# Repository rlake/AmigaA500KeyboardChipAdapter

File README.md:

Amiga A500 Keyboard Chip Adapter

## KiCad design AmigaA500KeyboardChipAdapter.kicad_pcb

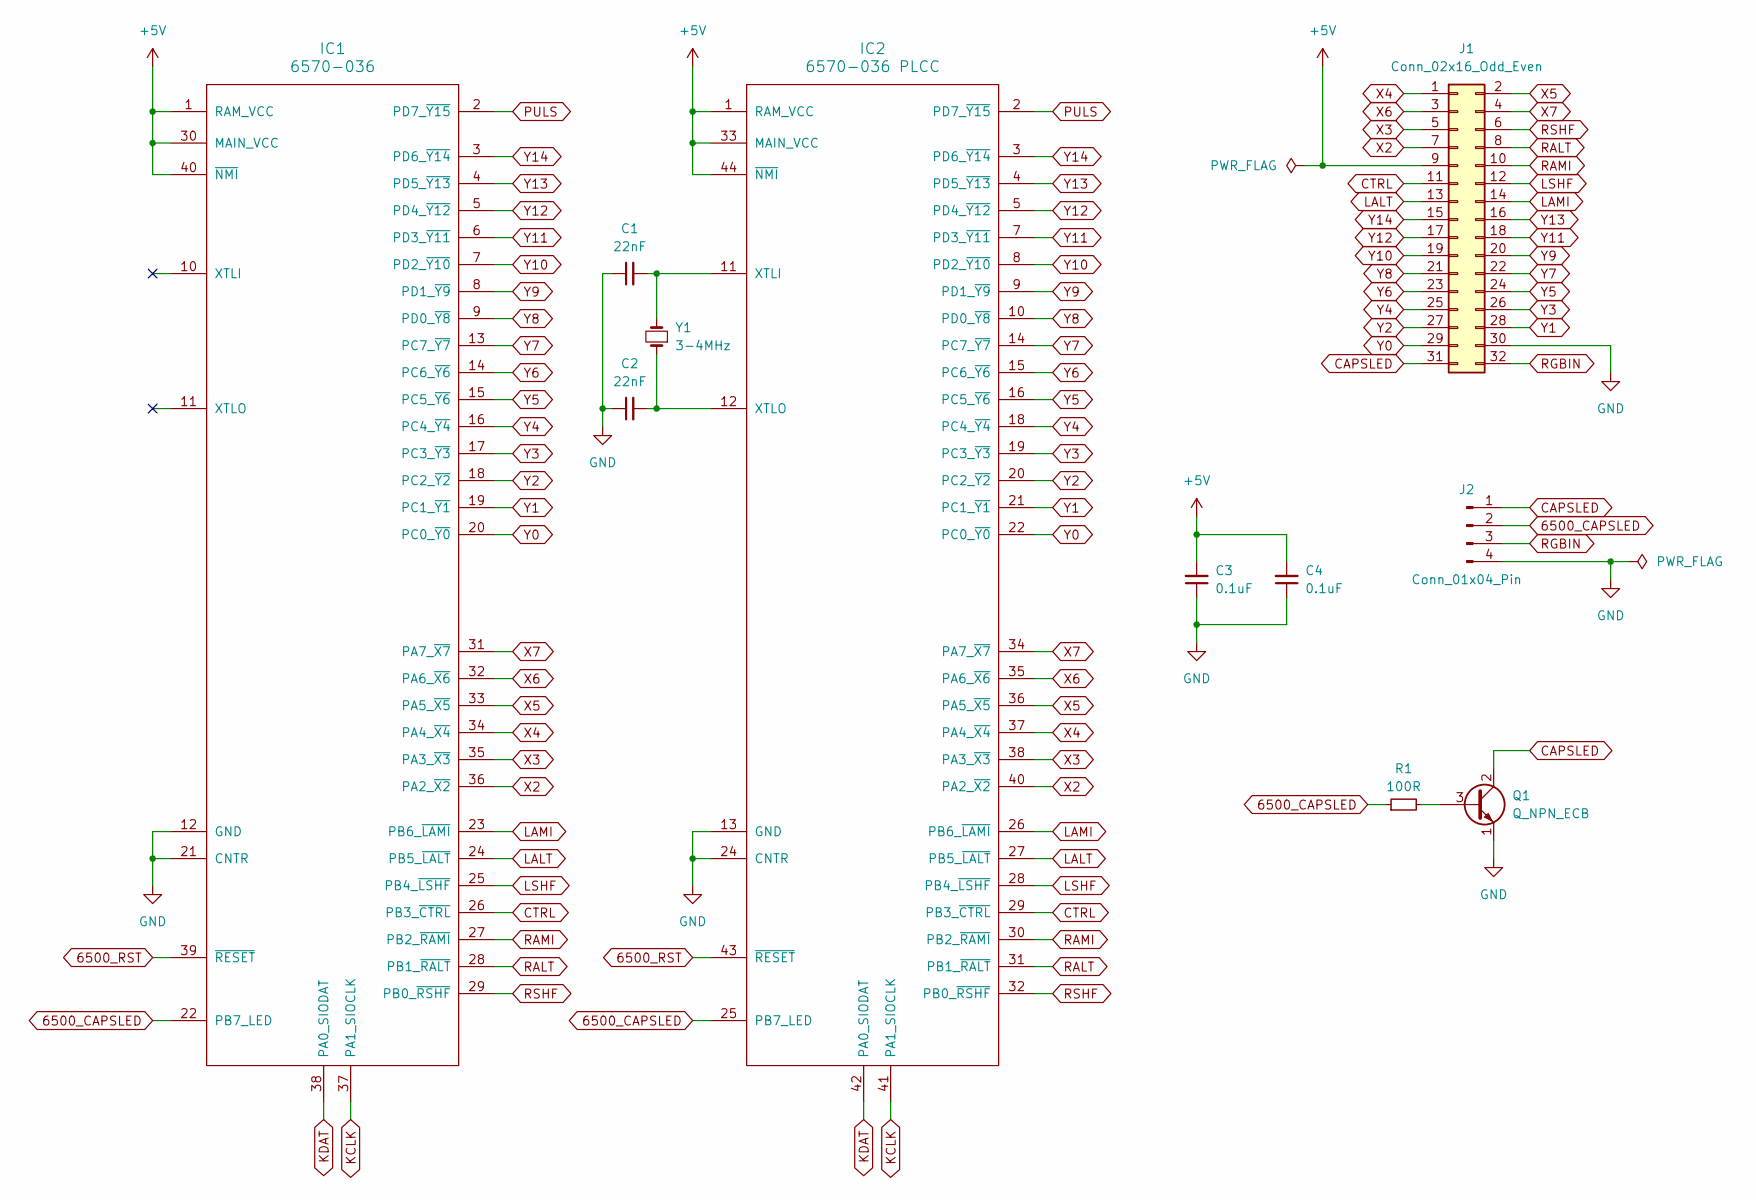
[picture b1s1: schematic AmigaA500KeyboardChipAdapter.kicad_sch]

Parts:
C1, C2: 22nF; C_Disc_D5.0mm_W2.5mm_P5.00mm
C3, C4: 0.1uF; C_Disc_D5.0mm_W2.5mm_P5.00mm
IC1: 6570-036; DIP-40_W15.24mm
IC2: 6570-036 PLCC; PLCC-44_THT-Socket
J1: Conn_02x16_Odd_Even; PinHeader_2x16_P2.54mm_Vertical
J2: Conn_01x04_Pin; PinHeader_1x04_P2.54mm_Horizontal
Q1: Q_NPN_ECB; TO-92_Inline_Wide
R1: 100R; R_Axial_DIN0207_L6.3mm_D2.5mm_P10.16mm_Horizontal
Y1: 3-4MHz; Crystal_HC49-U_Vertical

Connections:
6500_CAPSLED: IC1.22 (PB7_LED), IC2.25 (PB7_LED), J2.2, R1.1
6500_RST: IC1.39 (~RESET), IC2.43 (~RESET)
+5V: C3.2, C4.2, IC1.1 (RAM_VCC), IC1.30 (MAIN_VCC), IC1.40 (~NMI), IC2.1 (RAM_VCC), IC2.33 (MAIN_VCC), IC2.44 (~NMI), J1.9
CAPSLED: J1.31, J2.1, Q1.2 (C)
CTRL: IC1.26 (PB3_~CTRL), IC2.29 (PB3_~CTRL), J1.11
GND: C1.1, C2.1, C3.1, C4.1, IC1.12 (GND), IC1.21 (CNTR), IC2.13 (GND), IC2.24 (CNTR), J1.30, J2.4, Q1.1 (E)
KCLK: IC1.37 (PA1_SIOCLK), IC2.41 (PA1_SIOCLK)
KDAT: IC1.38 (PA0_SIODAT), IC2.42 (PA0_SIODAT)
LALT: IC1.24 (PB5_~LALT), IC2.27 (PB5_~LALT), J1.13
LAMI: IC1.23 (PB6_~LAMI), IC2.26 (PB6_~LAMI), J1.14
LSHF: IC1.25 (PB4_~LSHF), IC2.28 (PB4_~LSHF), J1.12
unnamed: C1.2, IC2.11 (XTLI), Y1.2
unnamed: C2.2, IC2.12 (XTLO), Y1.1
unnamed: Q1.3 (B), R1.2
PULS: IC1.2 (PD7_~Y15), IC2.2 (PD7_~Y15)
RALT: IC1.28 (PB1_~RALT), IC2.31 (PB1_~RALT), J1.8
RAMI: IC1.27 (PB2_~RAMI), IC2.30 (PB2_~RAMI), J1.10
RGBIN: J1.32, J2.3
RSHF: IC1.29 (PB0_~RSHF), IC2.32 (PB0_~RSHF), J1.6
X2: IC1.36 (PA2_~X2), IC2.40 (PA2_~X2), J1.7
X3: IC1.35 (PA3_~X3), IC2.38 (PA3_~X3), J1.5
X4: IC1.34 (PA4_~X4), IC2.37 (PA4_~X4), J1.1
X5: IC1.33 (PA5_~X5), IC2.36 (PA5_~X5), J1.2
X6: IC1.32 (PA6_~X6), IC2.35 (PA6_~X6), J1.3
X7: IC1.31 (PA7_~X7), IC2.34 (PA7_~X7), J1.4
Y0: IC1.20 (PC0_~Y0), IC2.22 (PC0_~Y0), J1.29
Y1: IC1.19 (PC1_~Y1), IC2.21 (PC1_~Y1), J1.28
Y2: IC1.18 (PC2_~Y2), IC2.20 (PC2_~Y2), J1.27
Y3: IC1.17 (PC3_~Y3), IC2.19 (PC3_~Y3), J1.26
Y4: IC1.16 (PC4_~Y4), IC2.18 (PC4_~Y4), J1.25
Y5: IC1.15 (PC5_~Y6), IC2.16 (PC5_~Y6), J1.24
Y6: IC1.14 (PC6_~Y6), IC2.15 (PC6_~Y6), J1.23
Y7: IC1.13 (PC7_~Y7), IC2.14 (PC7_~Y7), J1.22
Y8: IC1.9 (PD0_~Y8), IC2.10 (PD0_~Y8), J1.21
Y9: IC1.8 (PD1_~Y9), IC2.9 (PD1_~Y9), J1.20
Y10: IC1.7 (PD2_~Y10), IC2.8 (PD2_~Y10), J1.19
Y11: IC1.6 (PD3_~Y11), IC2.7 (PD3_~Y11), J1.18
Y12: IC1.5 (PD4_~Y12), IC2.5 (PD4_~Y12), J1.17
Y13: IC1.4 (PD5_~Y13), IC2.4 (PD5_~Y13), J1.16
Y14: IC1.3 (PD6_~Y14), IC2.3 (PD6_~Y14), J1.15

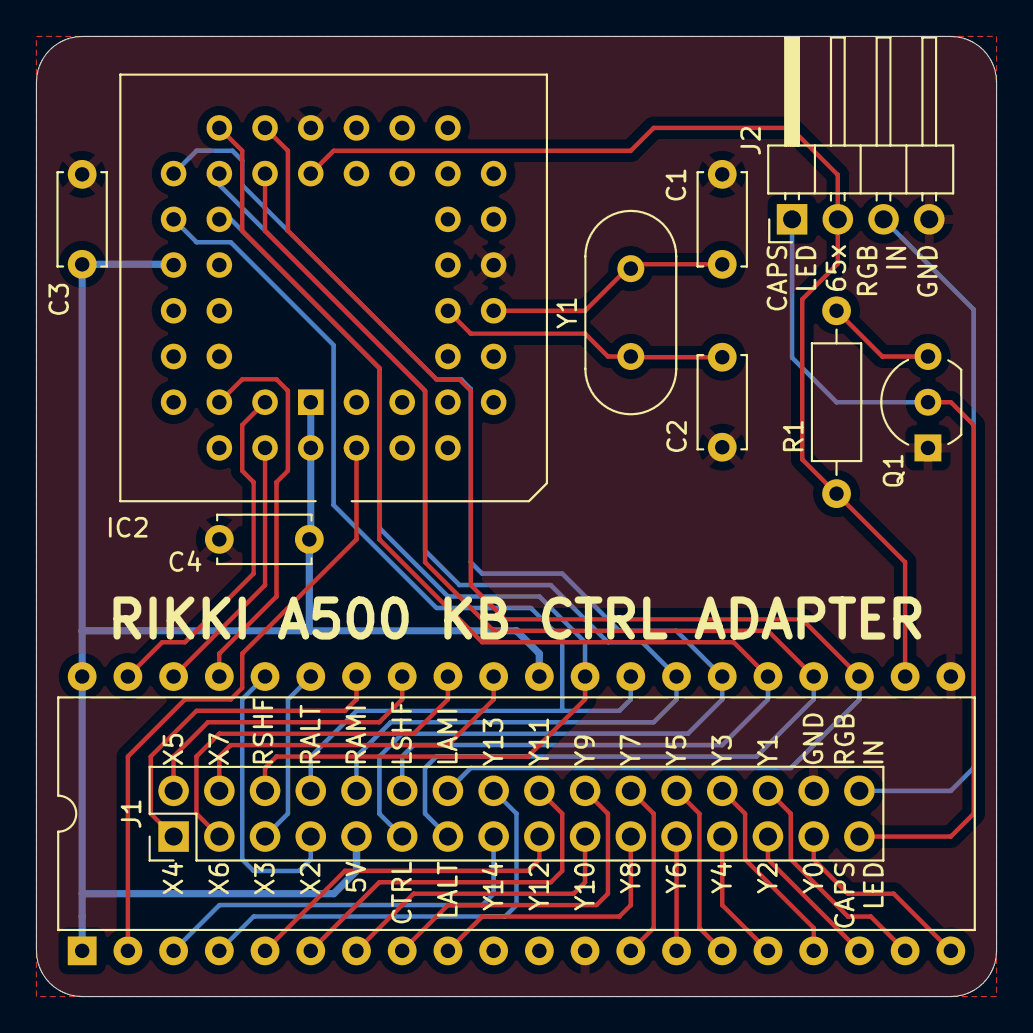
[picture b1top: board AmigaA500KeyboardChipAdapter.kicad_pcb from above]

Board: 4 copper layers, 53.3 x 53.3 mm, 11 parts (0 on the bottom side), 40 nets.

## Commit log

2024-12-14 Initial KiCad project
2024-12-14 Add symbols for controller chip
2024-12-14 Amiga A500 Keyboard Chip Adapter
